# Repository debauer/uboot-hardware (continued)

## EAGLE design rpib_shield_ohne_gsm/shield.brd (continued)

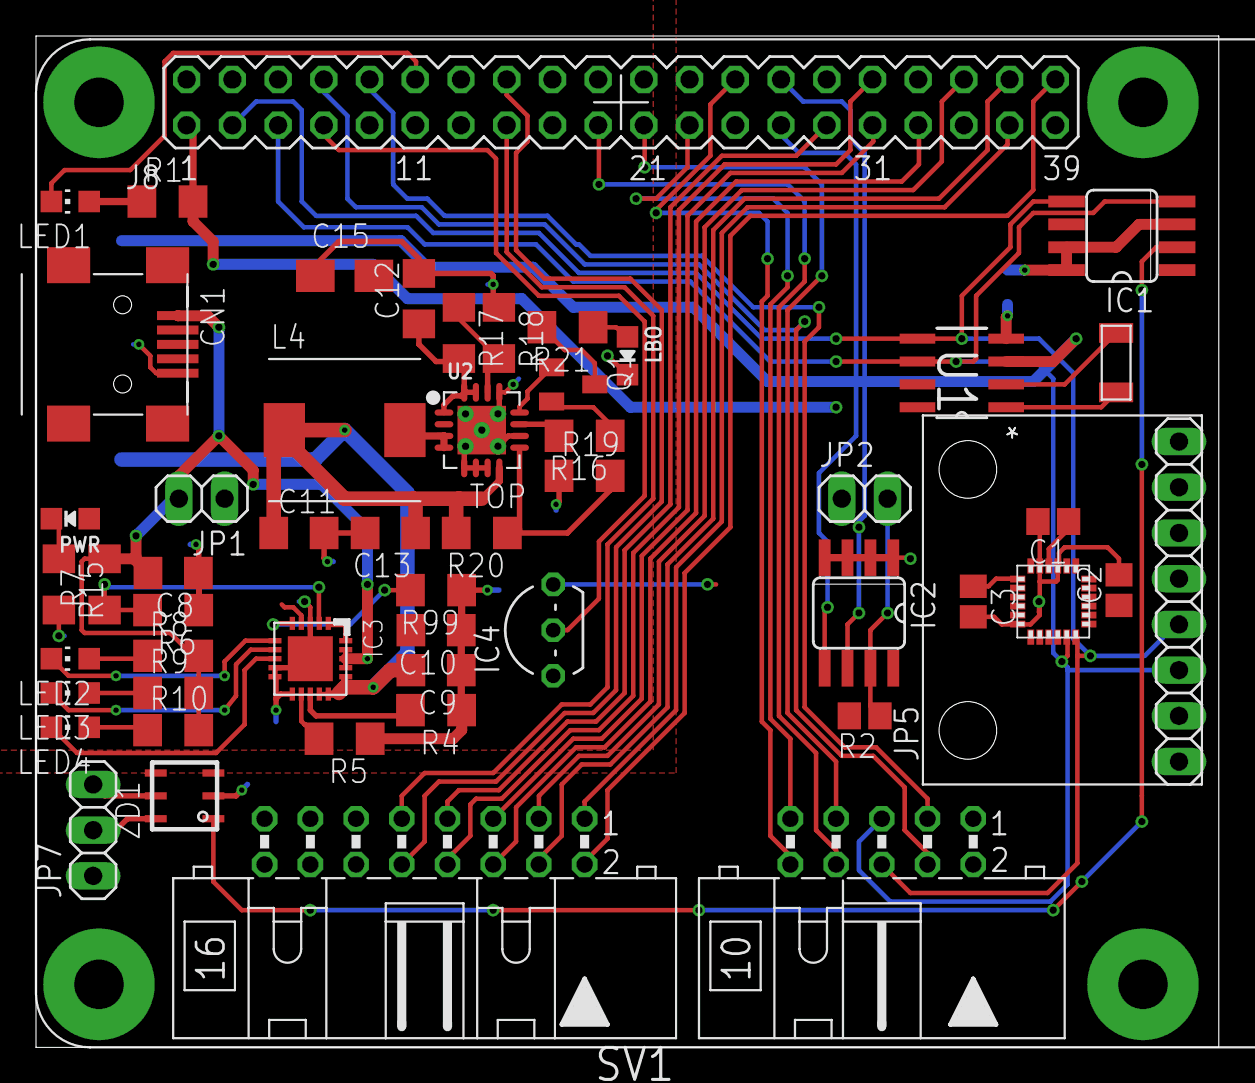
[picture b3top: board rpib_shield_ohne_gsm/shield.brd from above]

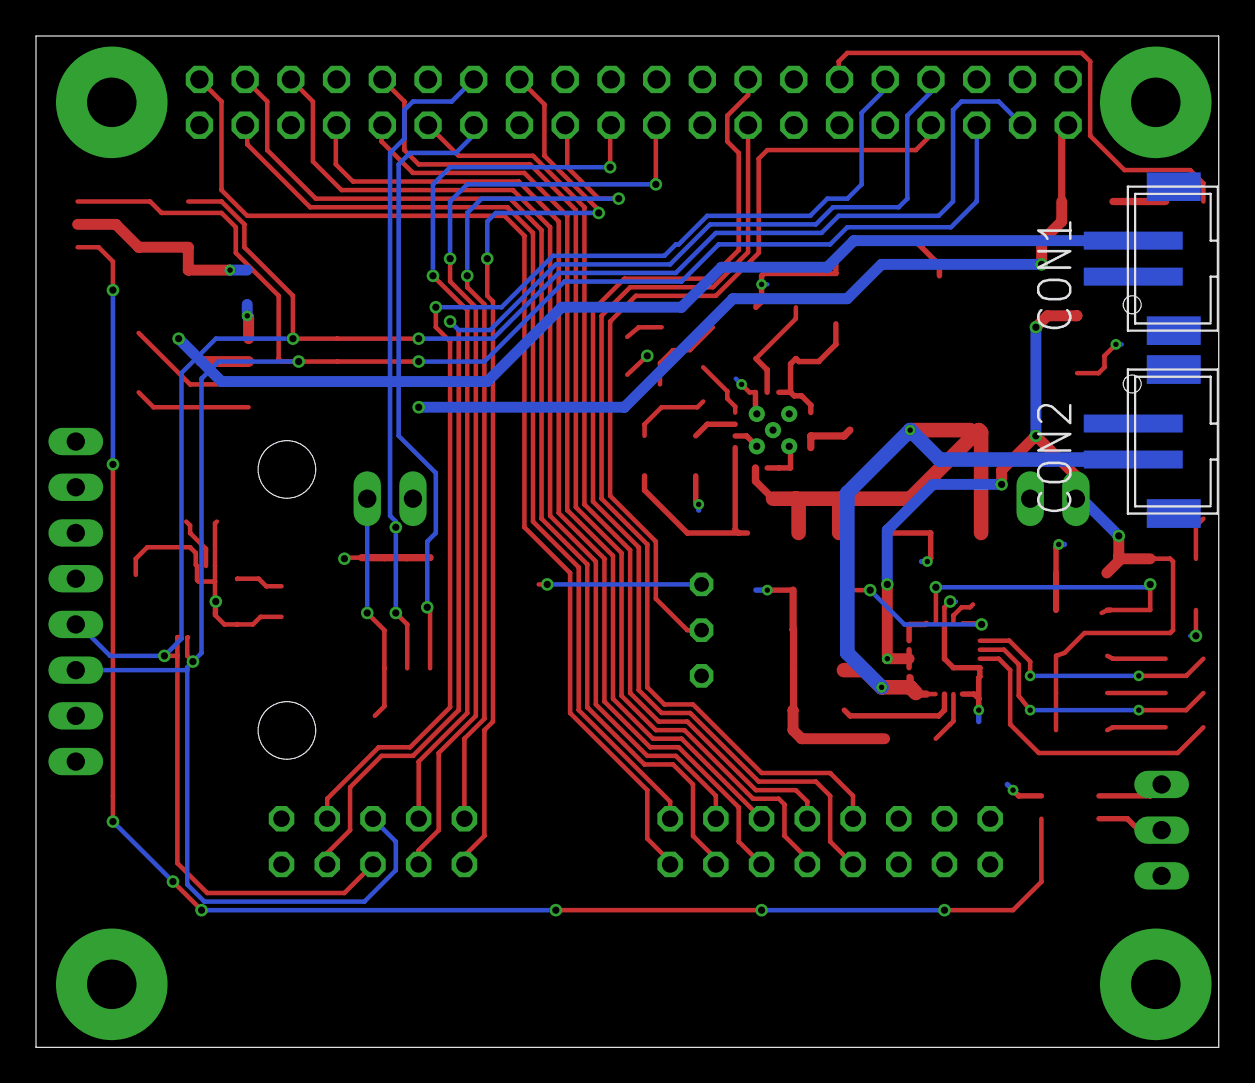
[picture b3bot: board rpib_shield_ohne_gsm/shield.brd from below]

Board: 2 copper layers, 65.7 x 56.2 mm, 54 parts (2 on the bottom side), 56 nets.

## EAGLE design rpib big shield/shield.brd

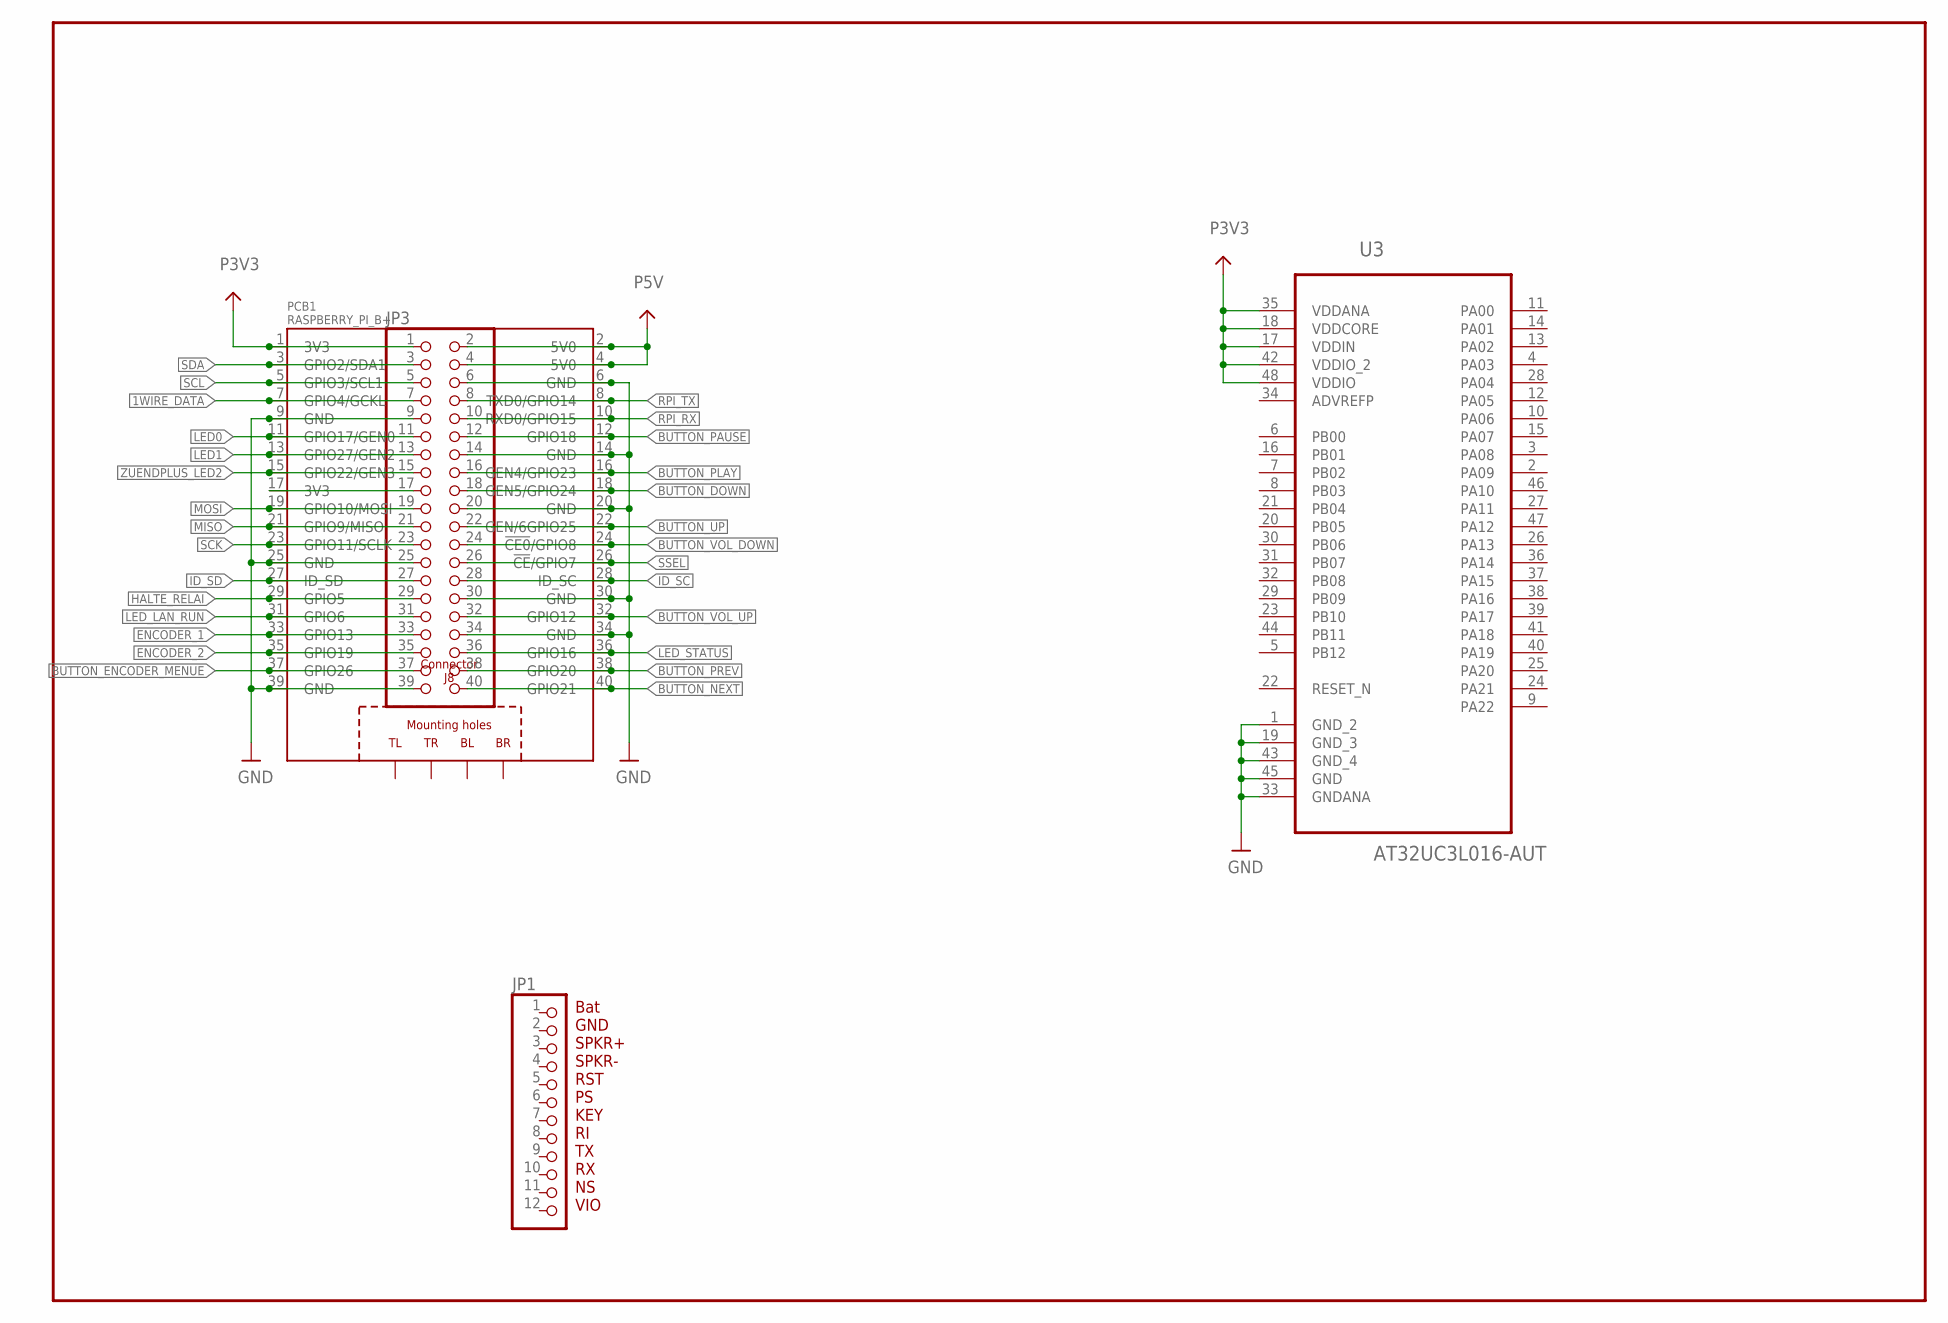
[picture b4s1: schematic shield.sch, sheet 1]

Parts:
JP1: ADAFRUIT-FONA; ADAFRUITFONA
JP3: PINHD-2X20; 2X20
PCB1: RASPBERRY_PI_B+
U3: AT32UC3L016-AUT; QFP50P900X900X120-48N

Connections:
1WIRE_DATA: JP3.7, PCB1.7 (GPIO4/GCKL); also elsewhere on the board
3V3@2: JP3.17, PCB1.17 (3V3)
ADVREFP: U3.34 (ADVREFP)
BUTTON_DOWN: JP3.18, PCB1.18 (GEN5/GPIO24); also elsewhere on the board
BUTTON_ENCODER_MENUE: JP3.37, PCB1.37 (GPIO26); also elsewhere on the board
BUTTON_NEXT: JP3.40, PCB1.40 (GPIO21); also elsewhere on the board
BUTTON_PAUSE: JP3.12, PCB1.12 (GPIO18); also elsewhere on the board
BUTTON_PLAY: JP3.16, PCB1.16 (GEN4/GPIO23); also elsewhere on the board
BUTTON_PREV: JP3.38, PCB1.38 (GPIO20); also elsewhere on the board
BUTTON_UP: JP3.22, PCB1.22 (GEN/6GPIO25); also elsewhere on the board
BUTTON_VOL_DOWN: JP3.24, PCB1.24 (!CE0!/GPIO8); also elsewhere on the board
BUTTON_VOL_UP: JP3.32, PCB1.32 (GPIO12); also elsewhere on the board
ENCODER_1: JP3.33, PCB1.33 (GPIO13)
ENCODER_2: JP3.35, PCB1.35 (GPIO19)
GND: JP3.6, JP3.14, JP3.20, JP3.30, JP3.34, PCB1.6 (GND), PCB1.14 (GND), PCB1.20 (GND), PCB1.30 (GND), PCB1.34 (GND), U3.1 (GND_2), U3.19 (GND_3), U3.33 (GNDANA), U3.43 (GND_4), U3.45 (GND); also elsewhere on the board
GND@1: JP3.9, JP3.25, JP3.39, PCB1.9 (GND), PCB1.25 (GND), PCB1.39 (GND); also elsewhere on the board
HALTE_RELAI: JP3.29, PCB1.29 (GPIO5); also elsewhere on the board
ID_SC: JP3.28, PCB1.28 (ID_SC); also elsewhere on the board
ID_SD: JP3.27, PCB1.27 (ID_SD); also elsewhere on the board
LED0: JP3.11, PCB1.11 (GPIO17/GEN0)
LED1: JP3.13, PCB1.13 (GPIO27/GEN2)
LED_LAN_RUN: JP3.31, PCB1.31 (GPIO6)
LED_STATUS: JP3.36, PCB1.36 (GPIO16)
MISO: JP3.21, PCB1.21 (GPIO9/MISO); also elsewhere on the board
MOSI: JP3.19, PCB1.19 (GPIO10/MOSI); also elsewhere on the board
P3V3: JP3.1, PCB1.1 (3V3), U3.17 (VDDIN), U3.18 (VDDCORE), U3.35 (VDDANA), U3.42 (VDDIO_2), U3.48 (VDDIO); also elsewhere on the board
P5V: JP3.2, JP3.4, PCB1.2 (5V0), PCB1.4 (5V0); also elsewhere on the board
RPI_RX: JP3.10, PCB1.10 (RXD0/GPIO15); also elsewhere on the board
RPI_TX: JP3.8, PCB1.8 (TXD0/GPIO14); also elsewhere on the board
SCK: JP3.23, PCB1.23 (GPIO11/SCLK); also elsewhere on the board
SCL: JP3.5, PCB1.5 (GPIO3/SCL1); also elsewhere on the board
SDA: JP3.3, PCB1.3 (GPIO2/SDA1); also elsewhere on the board
SSEL: JP3.26, PCB1.26 (!CE!/GPIO7); also elsewhere on the board
ZUENDPLUS_LED2: JP3.15, PCB1.15 (GPIO22/GEN3); also elsewhere on the board

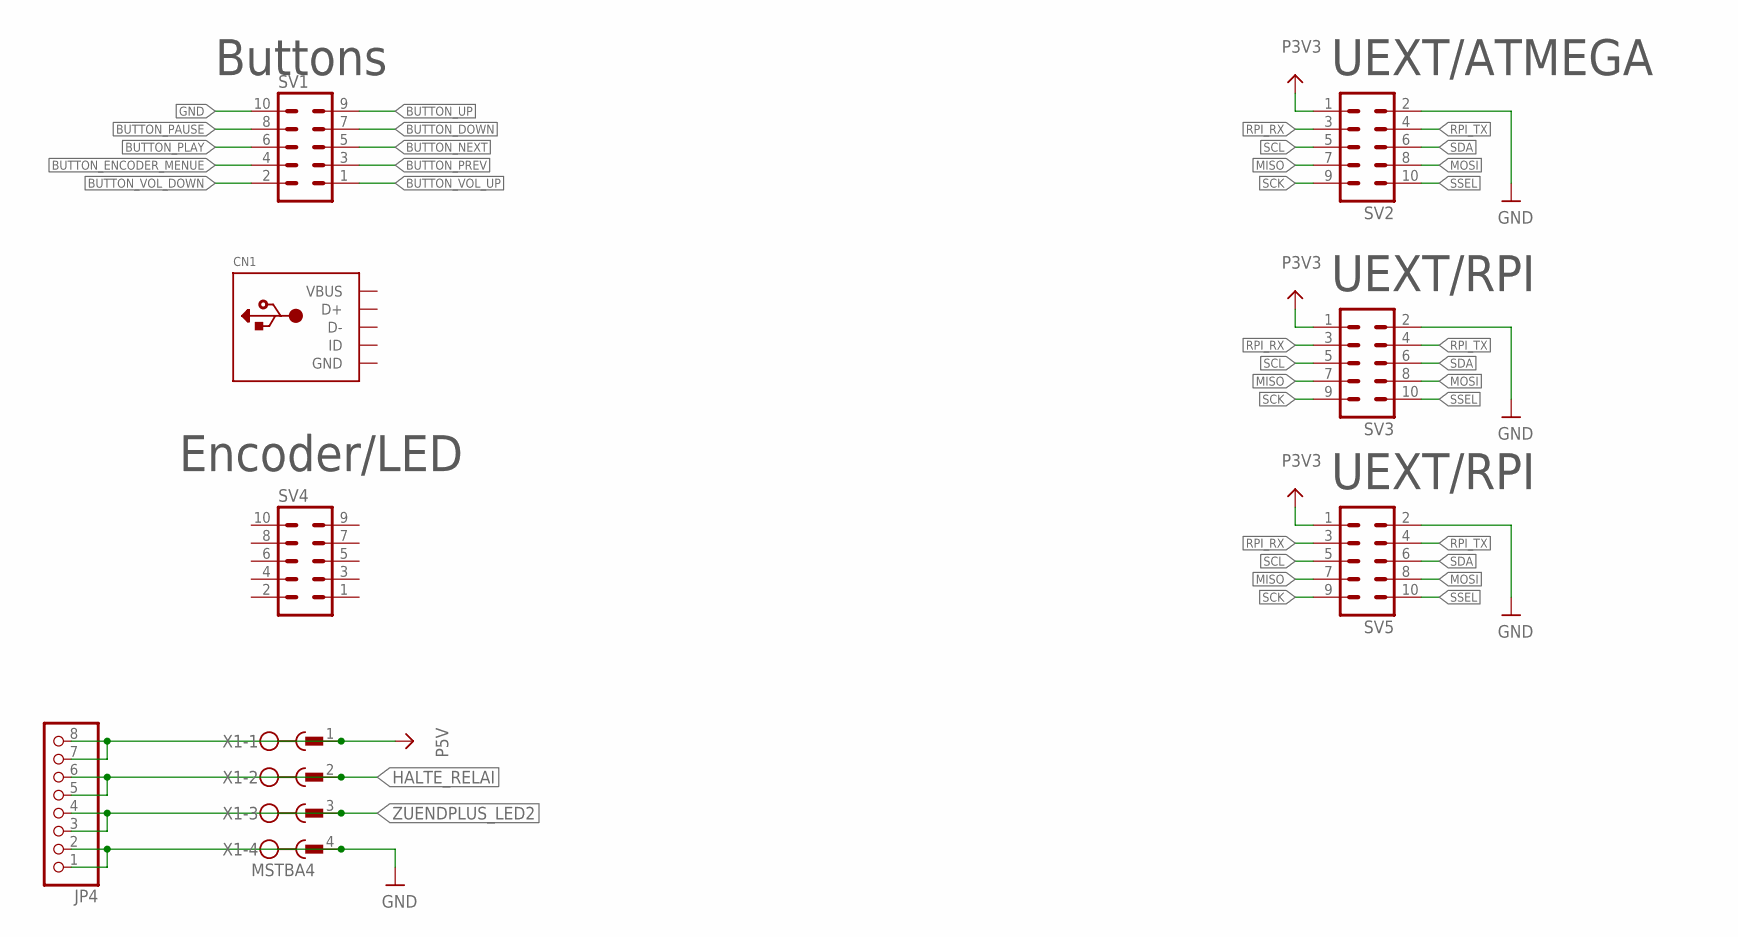
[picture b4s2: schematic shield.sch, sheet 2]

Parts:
CN1: USBMINIB; USB-MINIB
JP4: PINHD-1X8/90; 1X08/90
SV1, SV2, SV3, SV4, SV5: ML10
X1: MSTBA4

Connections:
BUTTON_DOWN: SV1.7; also elsewhere on the board
BUTTON_ENCODER_MENUE: SV1.4; also elsewhere on the board
BUTTON_NEXT: SV1.5; also elsewhere on the board
BUTTON_PAUSE: SV1.8; also elsewhere on the board
BUTTON_PLAY: SV1.6; also elsewhere on the board
BUTTON_PREV: SV1.3; also elsewhere on the board
BUTTON_UP: SV1.9; also elsewhere on the board
BUTTON_VOL_DOWN: SV1.2; also elsewhere on the board
BUTTON_VOL_UP: SV1.1; also elsewhere on the board
GND: JP4.1, JP4.2, SV1.10, SV2.2, SV3.2, SV5.2, X1.4; also elsewhere on the board
GND@1: CN1.GND; also elsewhere on the board
HALTE_RELAI: JP4.5, JP4.6, X1.2; also elsewhere on the board
MISO: SV2.7, SV3.7, SV5.7; also elsewhere on the board
MOSI: SV2.8, SV3.8, SV5.8; also elsewhere on the board
P3V3: SV2.1, SV3.1, SV5.1; also elsewhere on the board
P5V: JP4.7, JP4.8, X1.1; also elsewhere on the board
RPI_RX: SV2.3, SV3.3, SV5.3; also elsewhere on the board
RPI_TX: SV2.4, SV3.4, SV5.4; also elsewhere on the board
SCK: SV2.9, SV3.9, SV5.9; also elsewhere on the board
SCL: SV2.5, SV3.5, SV5.5; also elsewhere on the board
SDA: SV2.6, SV3.6, SV5.6; also elsewhere on the board
SSEL: SV2.10, SV3.10, SV5.10; also elsewhere on the board
VBUS: CN1.VBUS
ZUENDPLUS_LED2: JP4.3, JP4.4, X1.3; also elsewhere on the board

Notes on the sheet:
UEXT/ATMEGA
UEXT/RPI
Buttons
Encoder/LED

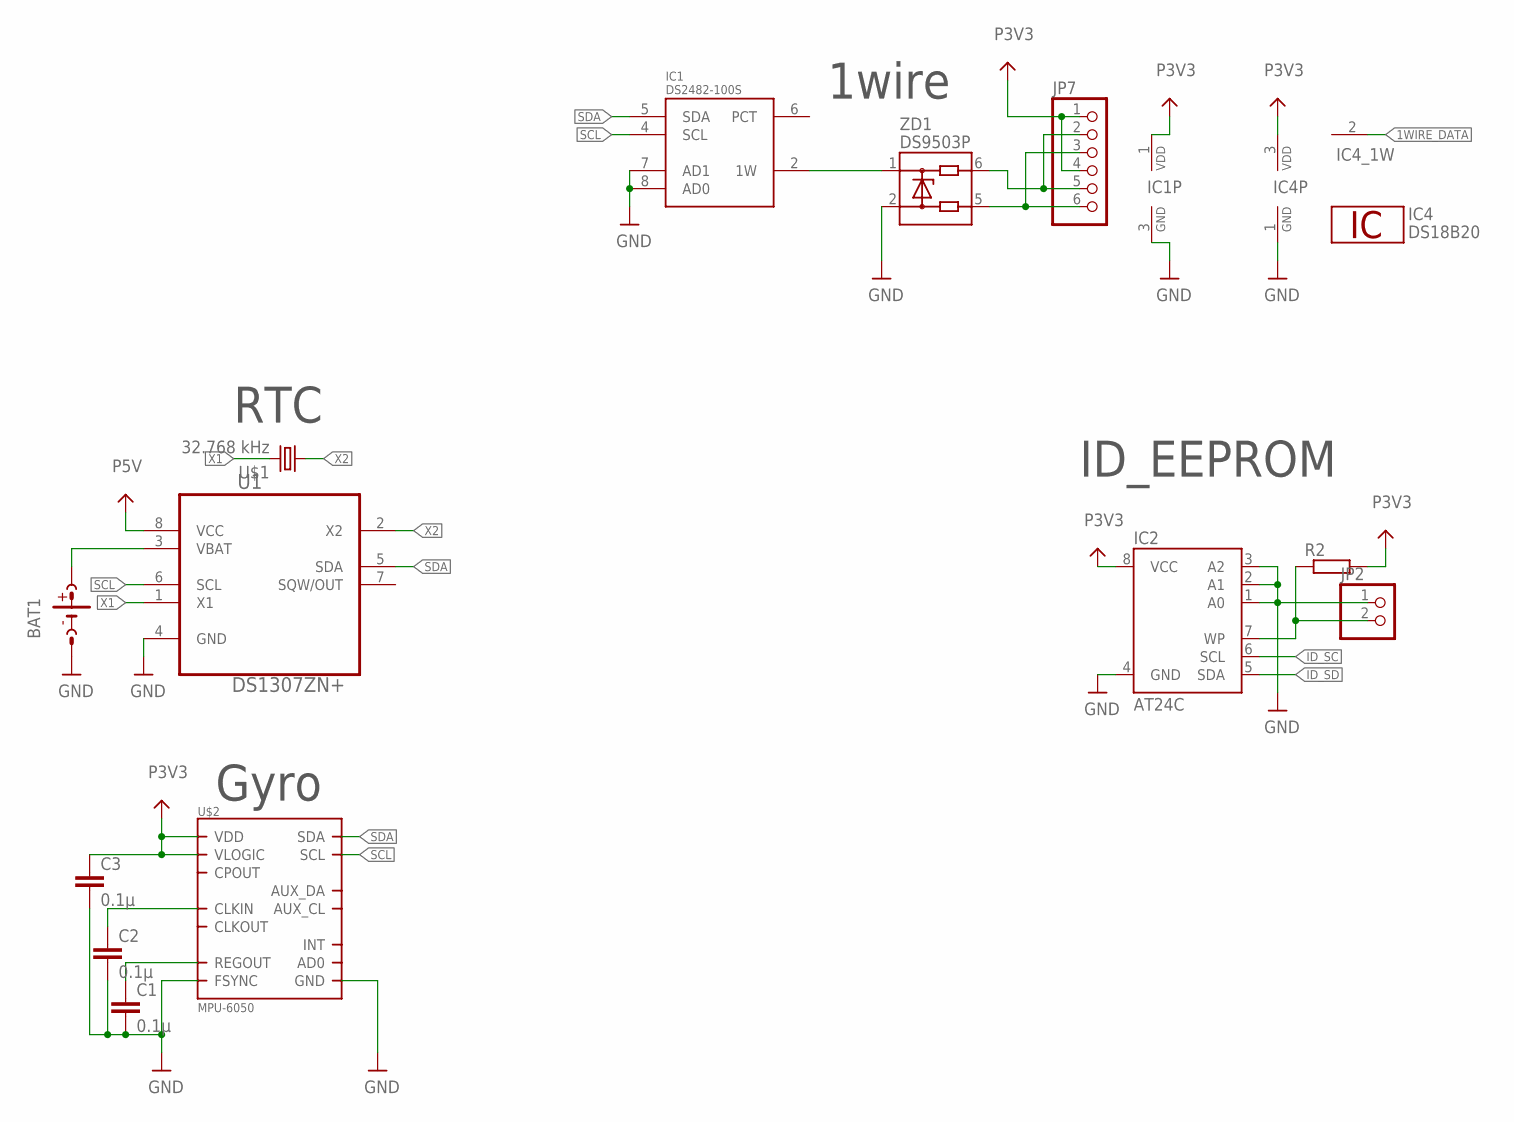
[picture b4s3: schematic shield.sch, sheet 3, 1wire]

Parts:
BAT1: CR2032; CR2032-SOCKET
C1, C2, C3: 0.1µ; C0805
IC1: DS2482-100S; SO08
IC2: AT24C; SO08
IC4: DS18B20; TO92-
JP2: PINHD-1X2; 1X02
JP7: PINHD-1X6/90; 1X06/90
R2: R-EU_R0805; R0805
U1: DS1307ZN+; SOIC127P600X175-8N
U$1: 32.768 kHz; CC5
U$2: MPU-6050; QFN.24.4X4
ZD1: DS9503P; TSOC6

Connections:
1WIRE_DATA: IC1.2 (1W), IC4.2 (1W), ZD1.1; also elsewhere on the board
GND: BAT1.M (NEG), C1.2, C2.2, C3.2, IC1.3 (GND), IC1.7 (AD1), IC1.8 (AD0), IC2.1 (A0), IC2.2 (A1), IC2.3 (A2), IC2.4 (GND), IC4.1 (GND), JP2.1, U1.4 (GND), U$2.11 (FSYNC), U$2.18 (GND), ZD1.2; also elsewhere on the board
ID_SC: IC2.6 (SCL); also elsewhere on the board
ID_SD: IC2.5 (SDA); also elsewhere on the board
unnamed: BAT1.P (POS2), U1.3 (VBAT)
unnamed: JP7.3, JP7.6, ZD1.5
unnamed: C1.1, U$2.10 (REGOUT)
unnamed: C2.1, U$2.1 (CLKIN)
unnamed: IC2.7 (WP), JP2.2, R2.1
unnamed: JP7.2, JP7.5, ZD1.6
P3V3: C3.1, IC1.1 (VDD), IC2.8 (VCC), IC4.3 (VDD), JP7.1, JP7.4, R2.2, U$2.8 (VLOGIC), U$2.13 (VDD); also elsewhere on the board
P5V: U1.8 (VCC); also elsewhere on the board
SCL: IC1.4 (SCL), U1.6 (SCL), U$2.23 (SCL); also elsewhere on the board
SDA: IC1.5 (SDA), U1.5 (SDA), U$2.24 (SDA); also elsewhere on the board
X1: U1.1 (X1), U$1.P$2 (2)
X2: U1.2 (X2), U$1.P$1 (1)

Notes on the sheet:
1wire
RTC
Gyro
ID_EEPROM

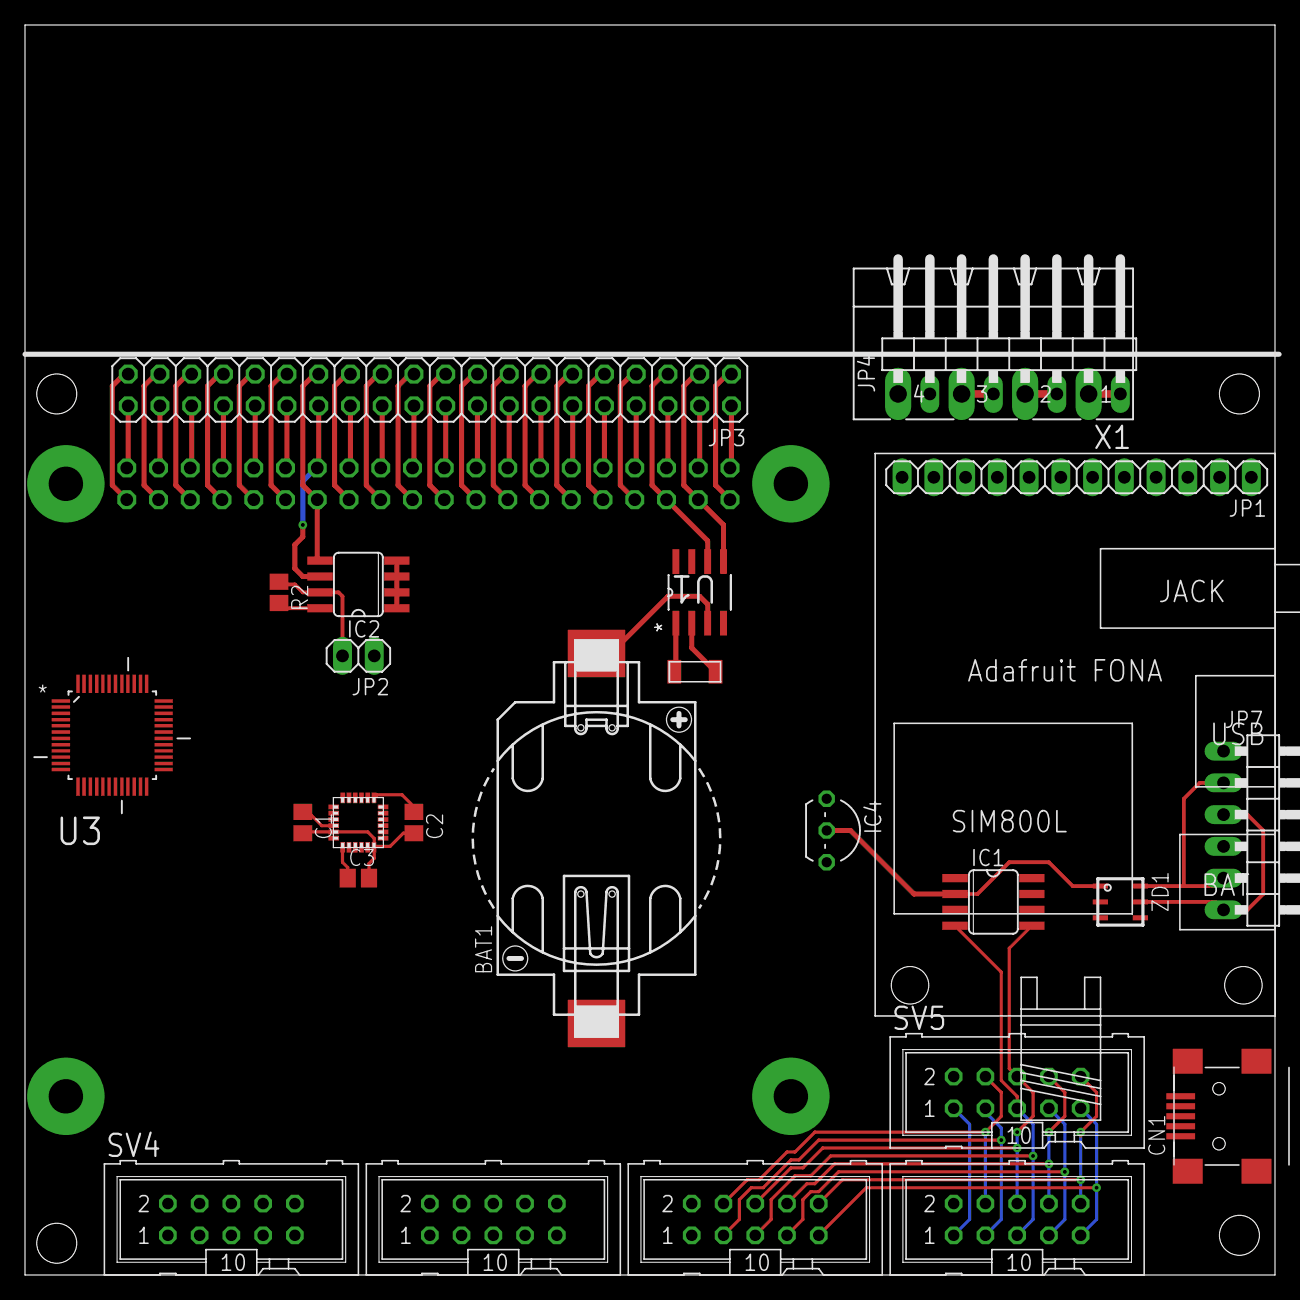
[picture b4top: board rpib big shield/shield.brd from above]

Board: 2 copper layers, 100.0 x 100.0 mm, 26 parts (1 on the bottom side), 41 nets.

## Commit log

2015-07-22 lipo charger and Sepic
2019-01-29 unknown old changes
